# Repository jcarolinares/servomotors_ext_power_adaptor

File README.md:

# servomotors_ext_power_adaptor
A simple adaptor to connect up to 16 servomotors using the 3 pins connectors to an external power and extract the signal to the board

Credits to Luis Díaz Ugena

CC-BY-SA

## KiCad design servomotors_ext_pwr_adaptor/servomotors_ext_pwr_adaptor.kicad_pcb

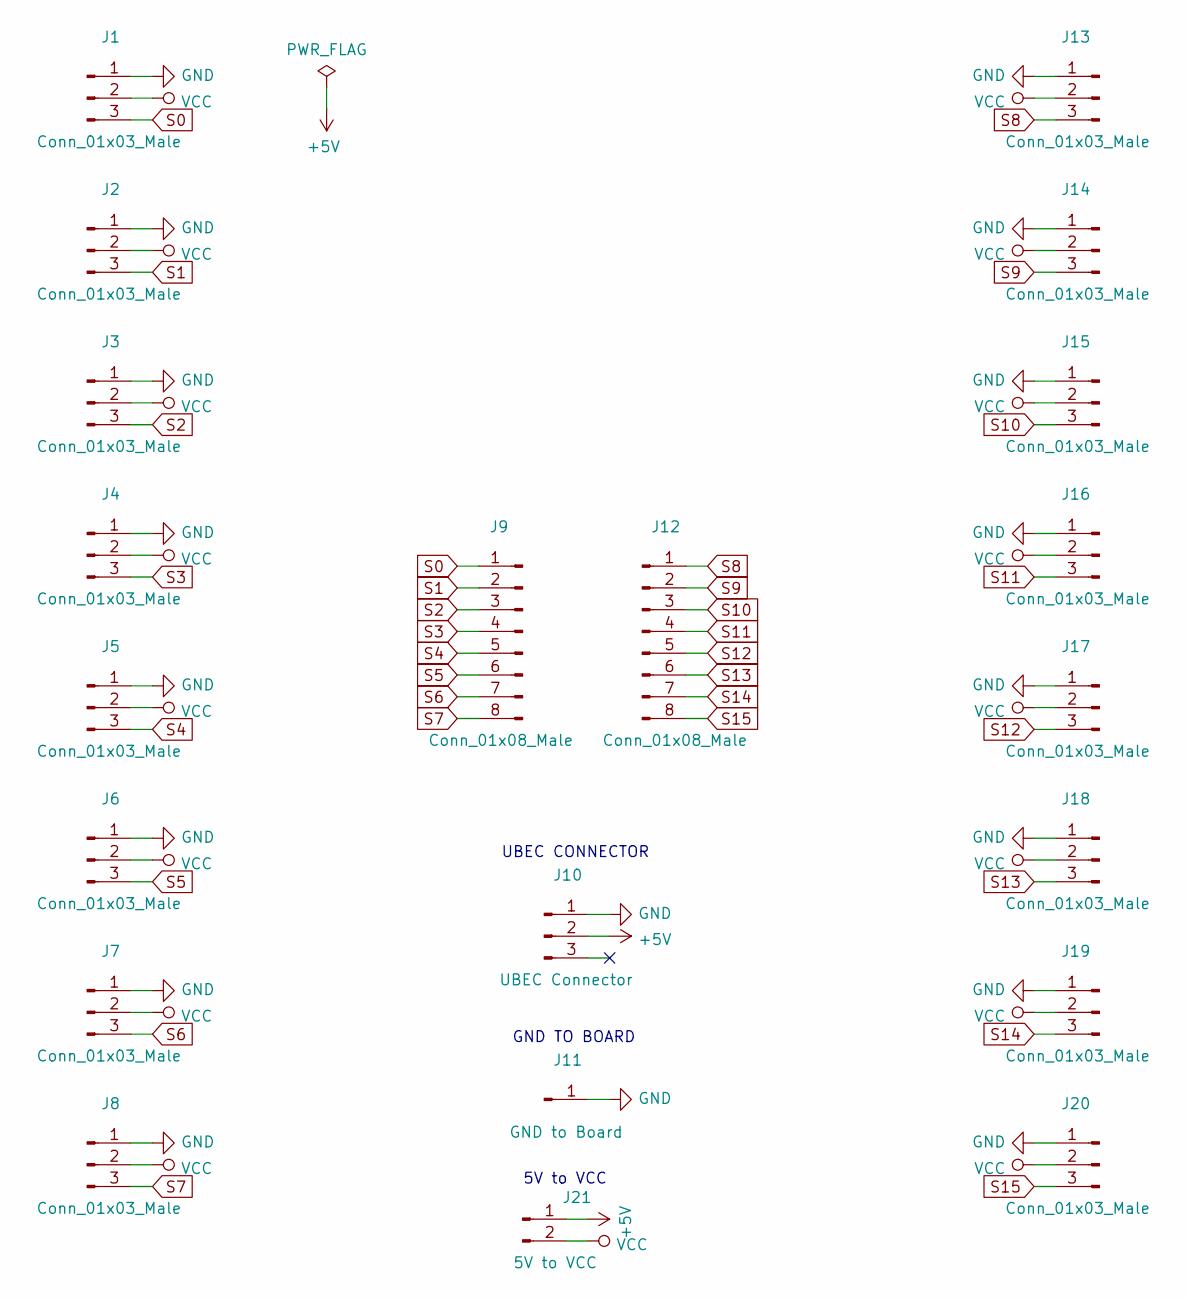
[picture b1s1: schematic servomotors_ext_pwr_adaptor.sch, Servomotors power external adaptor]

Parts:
J1, J2, J3, J4, J5, J6, J7, J8, J13, J14, J15, J16, J17, J18, J19, J20: Conn_01x03_Male; PinHeader_1x03_P2.54mm_Vertical
J9, J12: Conn_01x08_Male; PinHeader_1x08_P2.54mm_Vertical
J10: UBEC Connector; PinHeader_1x03_P2.54mm_Vertical
J11: GND to Board; PinSocket_1x01_P2.54mm_Vertical
J21: 5V to VCC; PinHeader_1x02_P2.54mm_Vertical

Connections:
+5V: J10.2, J21.1
GND: J1.1, J2.1, J3.1, J4.1, J5.1, J6.1, J7.1, J8.1, J10.1, J11.1, J13.1, J14.1, J15.1, J16.1, J17.1, J18.1, J19.1, J20.1
S0: J1.3, J9.1
S1: J2.3, J9.2
S2: J3.3, J9.3
S3: J4.3, J9.4
S4: J5.3, J9.5
S5: J6.3, J9.6
S6: J7.3, J9.7
S7: J8.3, J9.8
S8: J12.1, J13.3
S9: J12.2, J14.3
S10: J12.3, J15.3
S11: J12.4, J16.3
S12: J12.5, J17.3
S13: J12.6, J18.3
S14: J12.7, J19.3
S15: J12.8, J20.3
VCC: J1.2, J2.2, J3.2, J4.2, J5.2, J6.2, J7.2, J8.2, J13.2, J14.2, J15.2, J16.2, J17.2, J18.2, J19.2, J20.2, J21.2

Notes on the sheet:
UBEC CONNECTOR
GND TO BOARD
5V to VCC

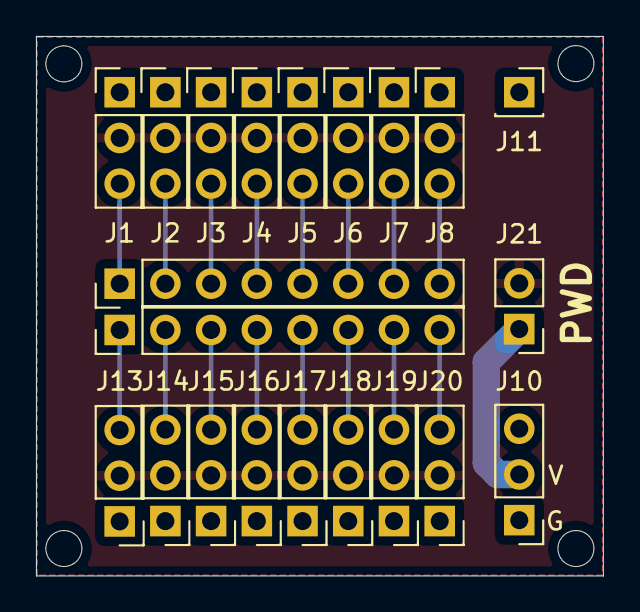
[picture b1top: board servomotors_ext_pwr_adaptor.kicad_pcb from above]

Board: 2 copper layers, 31.5 x 30.0 mm, 21 parts (0 on the bottom side), 19 nets.

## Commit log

2019-04-23 Schematic done. Symbols and footrpints added
2019-04-24 WIP PCB Almost done
2019-04-25 WIP Energy switch
2019-04-28 PCB done. Ready for QA and Gerber files
2019-04-28 Simple version done. Prepared for QA and Gerber files
2019-04-29 Gerbers done. Ready to order
2019-04-29 Gerbers done. Ready to order.
